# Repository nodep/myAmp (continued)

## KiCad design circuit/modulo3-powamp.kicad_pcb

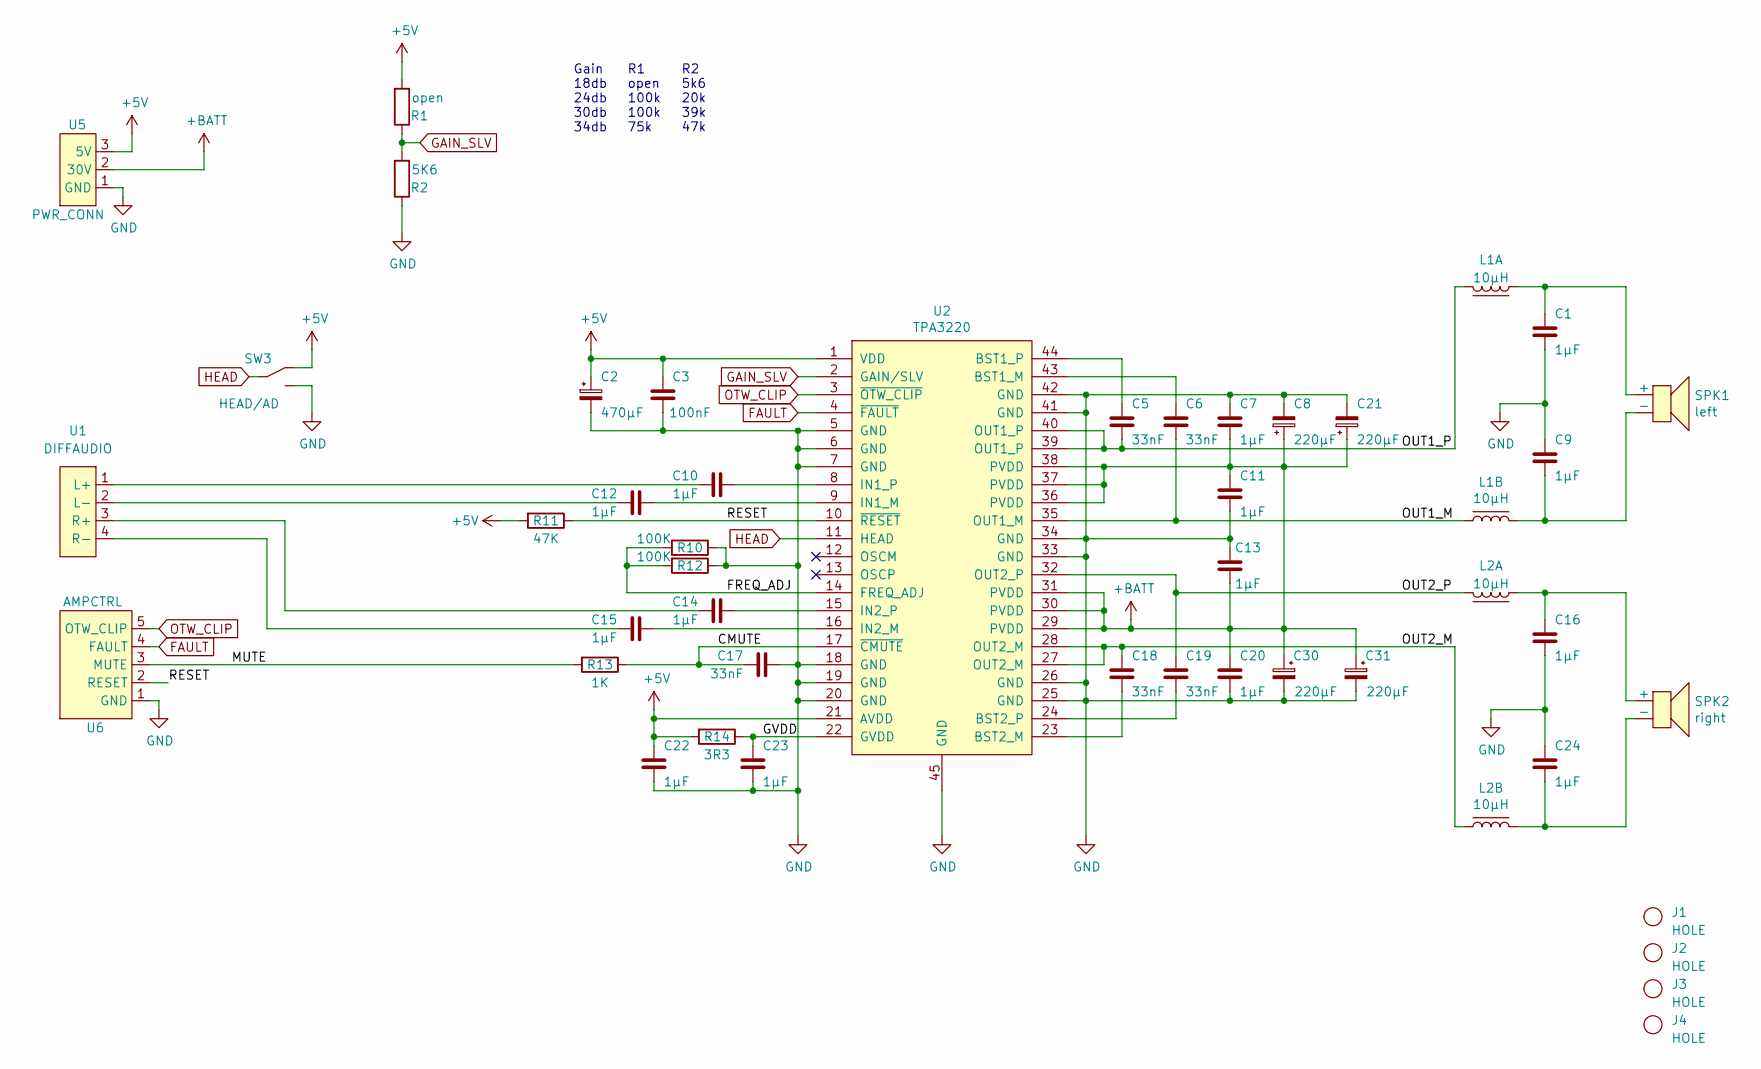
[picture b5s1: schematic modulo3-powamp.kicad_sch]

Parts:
C1, C9, C10, C12, C14, C15, C16, C24: 1μF; C_FILM_L7.2mm_W5.0mm_P5.00mm
C2: 470μF; CPOL_D8_P3.5
C3: 100nF; C_1206
C5, C6, C17, C18, C19: 33nF; C_1206
C7, C11, C13, C20, C22, C23: 1μF; C_1206
C8, C21, C30, C31: 220μF; CPOL_D10_P5
J1, J2, J3, J4: HOLE; MountingHole
L1, L2: 10μH; COILCRAFT-UA801x-AL
R1: open; R_10MM
R2: 5K6; R_10MM
R10, R12: 100K; R_10MM
R11: 47K; R_10MM
R13: 1K; R_10MM
R14: 3R3; R_0805
SPK1: left; SPKR_5MM_BLUE
SPK2: right; SPKR_5MM_BLUE
SW3: HEAD/AD; SW_SPDT_JUMPER
U1: DIFFAUDIO
U2: TPA3220; TSSOP-44_4.4x9.7mm_Pitch0.635mm_ThermalPad
U5: PWR_CONN
U6: AMPCTRL

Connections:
+5V: C2.1, C3.2, C22.1, R1.2, R11.2, R14.2, SW3.1, U2.1 (VDD), U2.21 (AVDD), U5.3 (5V)
+BATT: C7.2, C8.1, C11.1, C13.1, C20.1, C21.1, C30.1, C31.1, U2.29 (PVDD), U2.30 (PVDD), U2.31 (PVDD), U2.36 (PVDD), U2.37 (PVDD), U2.38 (PVDD), U5.2 (30V)
/CMUTE: C17.1, R13.1, U2.17 (~CMUTE)
/FREQ_ADJ: R10.2, R12.2, U2.14 (FREQ_ADJ)
/GVDD: C23.1, R14.1, U2.22 (GVDD)
/MUTE: R13.2, U6.3 (MUTE)
/OUT1_M: C6.2, L1.3, U2.35 (OUT1_M)
/OUT1_P: C5.2, L1.2, U2.39 (OUT1_P), U2.40 (OUT1_P)
/OUT2_M: C18.1, L2.3, U2.27 (OUT2_M), U2.28 (OUT2_M)
/OUT2_P: C19.1, L2.2, U2.32 (OUT2_P)
/RESET: R11.1, U2.10 (~RESET), U6.2 (RESET)
FAULT: U2.4 (~FAULT), U6.4 (FAULT)
GAIN_SLV: R1.1, R2.2, U2.2 (GAIN/SLV)
GND: C1.2, C2.2, C3.1, C7.1, C8.2, C9.1, C11.2, C13.2, C16.2, C17.2, C20.2, C21.2, C22.2, C23.2, C24.1, C30.2, C31.2, R2.1, R10.1, R12.1, SW3.3, U2.5 (GND), U2.6 (GND), U2.7 (GND), U2.18 (GND), U2.19 (GND), U2.20 (GND), U2.25 (GND), U2.26 (GND), U2.33 (GND), U2.34 (GND), U2.41 (GND), U2.42 (GND), U2.45 (GND), U5.1 (GND), U6.1 (GND)
HEAD: SW3.2, U2.11 (HEAD)
unnamed: C1.1, L1.1, SPK1.1 (+)
unnamed: C9.2, L1.4, SPK1.2 (-)
unnamed: C16.1, L2.1, SPK2.1 (+)
unnamed: C24.2, L2.4, SPK2.2 (-)
unnamed: C10.1, U1.1 (L+)
unnamed: C12.1, U1.2 (L-)
unnamed: C14.1, U1.3 (R+)
unnamed: C15.1, U1.4 (R-)
unnamed: C6.1, U2.43 (BST1_M)
unnamed: C5.1, U2.44 (BST1_P)
unnamed: C18.2, U2.23 (BST2_M)
unnamed: C19.2, U2.24 (BST2_P)
unnamed: C12.2, U2.9 (IN1_M)
unnamed: C10.2, U2.8 (IN1_P)
unnamed: C15.2, U2.16 (IN2_M)
unnamed: C14.2, U2.15 (IN2_P)
OTW_CLIP: U2.3 (~OTW_CLIP), U6.5 (OTW_CLIP)

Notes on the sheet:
Gain 18db 24db 30db 34db
R2 5k6 20k 39k 47k
R1 open 100k 100k 75k

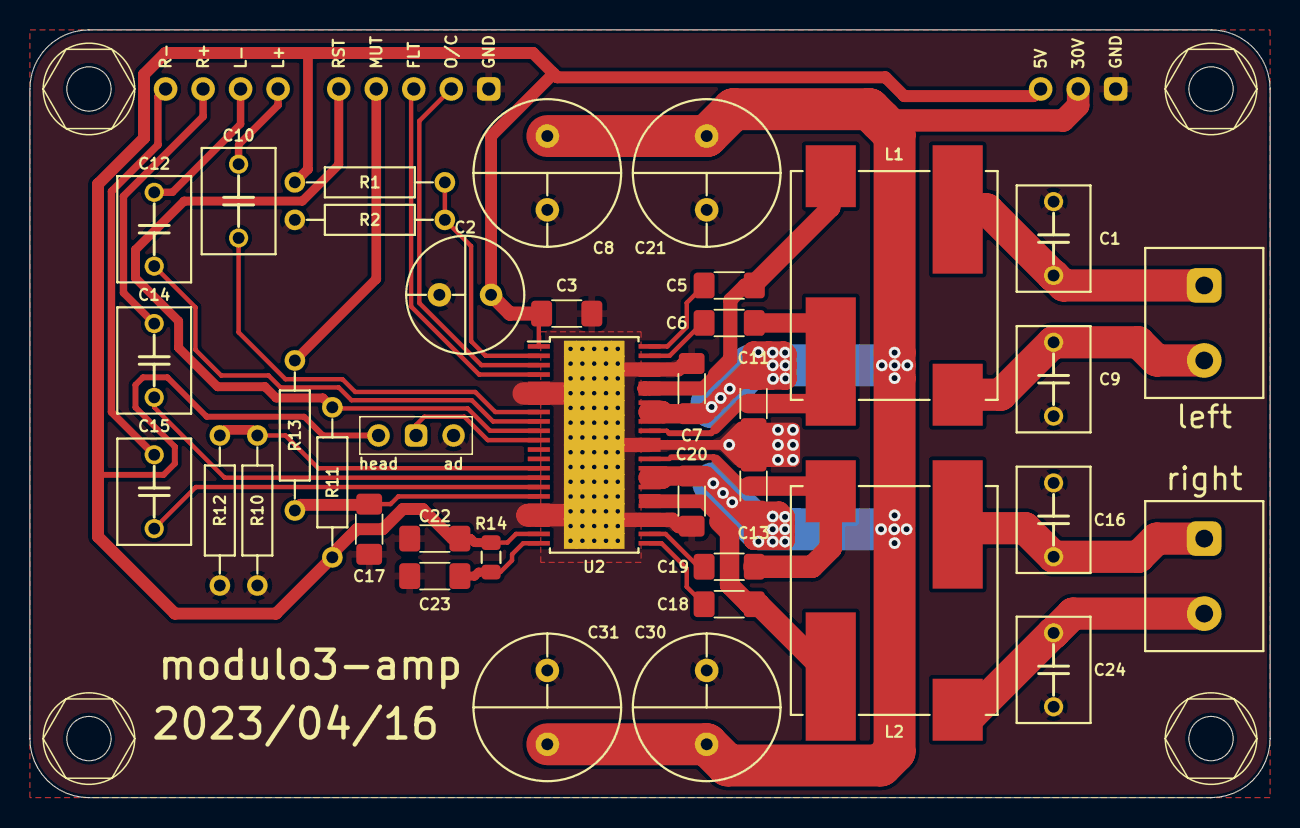
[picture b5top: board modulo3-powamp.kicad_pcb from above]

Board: 2 copper layers, 84.0 x 52.0 mm, 45 parts (0 on the bottom side), 32 nets.

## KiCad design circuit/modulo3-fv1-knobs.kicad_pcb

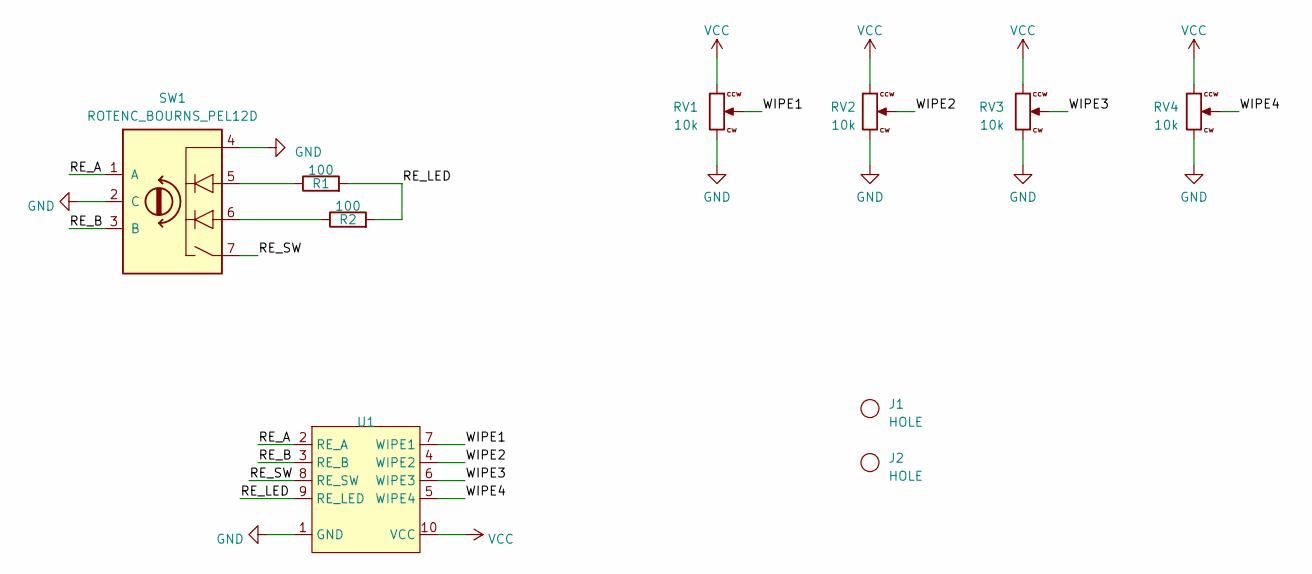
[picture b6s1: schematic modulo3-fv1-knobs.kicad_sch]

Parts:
J1, J2: HOLE; MountingHole
R1, R2: 100; R_10MM
RV1, RV2, RV3, RV4: 10k; BOURNS_PTD901_xx15K
SW1: ROTENC_BOURNS_PEL12D; BOURNS_PEL12D-2xxx
U1: KNOBS

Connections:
/RE_A: SW1.1 (A), U1.2 (RE_A)
/RE_B: SW1.3 (B), U1.3 (RE_B)
/RE_LED: R1.2, R2.2, U1.9 (RE_LED)
/RE_SW: SW1.7, U1.8 (RE_SW)
/WIPE1: RV1.2, U1.7 (WIPE1)
/WIPE2: RV2.2, U1.4 (WIPE2)
/WIPE3: RV3.2, U1.6 (WIPE3)
/WIPE4: RV4.2, U1.5 (WIPE4)
GND: RV1.3, RV2.3, RV3.3, RV4.3, SW1.2 (C), SW1.4, U1.1 (GND)
unnamed: R1.1, SW1.5
unnamed: R2.1, SW1.6
VCC: RV1.1, RV2.1, RV3.1, RV4.1, U1.10 (VCC)

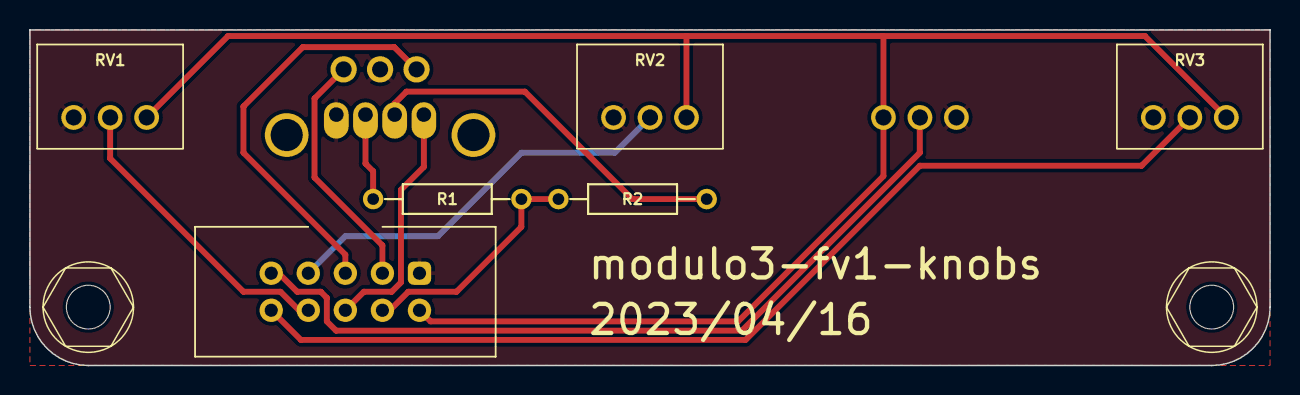
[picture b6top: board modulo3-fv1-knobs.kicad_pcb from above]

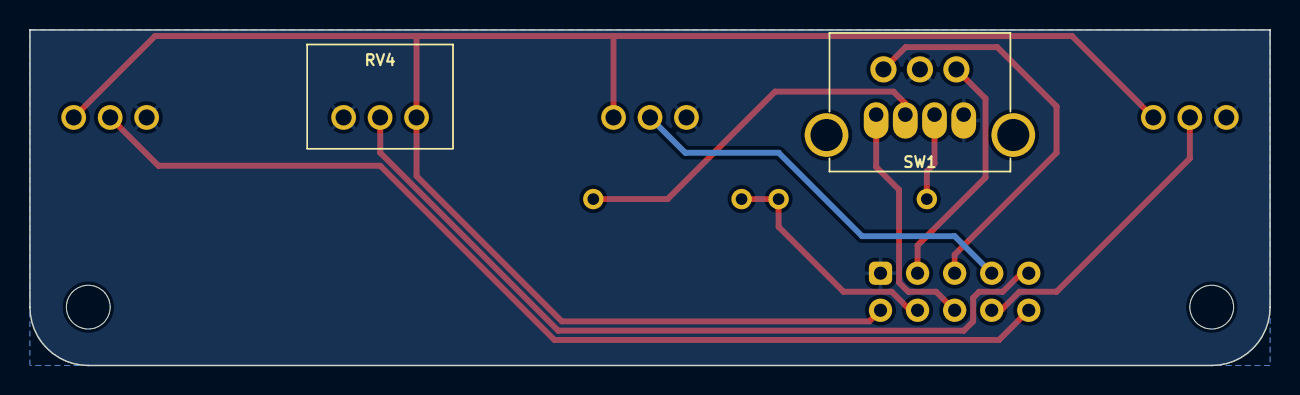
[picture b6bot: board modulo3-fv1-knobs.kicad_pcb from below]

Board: 2 copper layers, 85.0 x 23.0 mm, 10 parts (2 on the bottom side), 12 nets.

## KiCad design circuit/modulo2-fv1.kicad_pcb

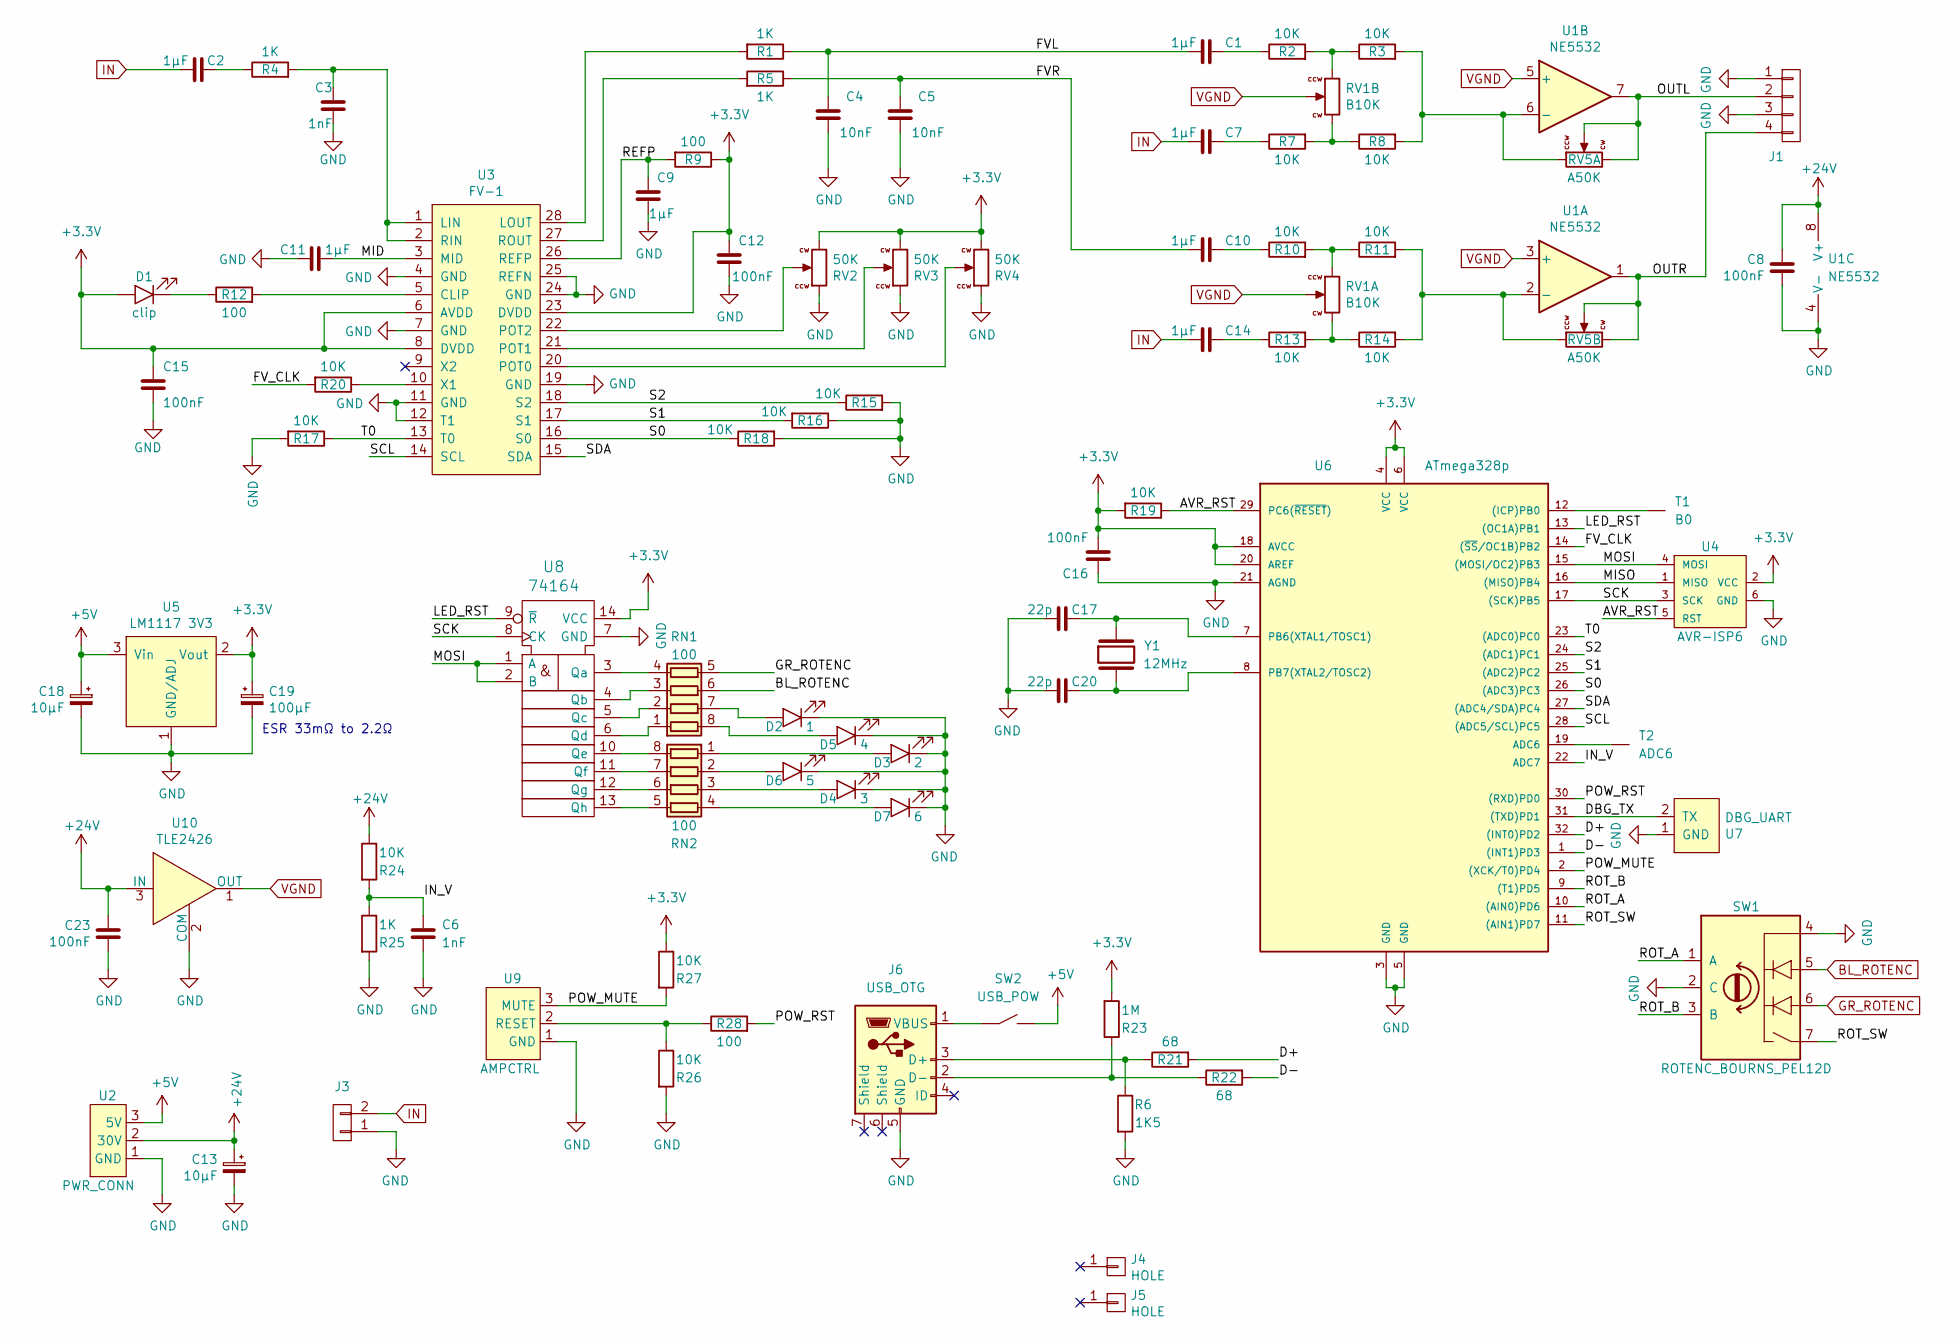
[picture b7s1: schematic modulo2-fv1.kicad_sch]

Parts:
C1, C2, C7, C10, C14: 1µF; C_FILM_L7.2mm_W5.0mm_P5.00mm
C3, C6: 1nF; C_1206
C4, C5: 10nF; C_1206
C8, C12, C15, C16: 100nF; C_1206
C9, C11: 1µF; C_1206
C13: 10µF; CPOL_D6.3_P2.5
C17, C20: 22p; C_5MM_1206
C18: 10µF; CPOL_D4_P1.5
C19: 100µF; CPOL_D6.3_P2.5
C23: 100nF; C_5MM_1206
D1: clip; LED_D3.0mm_Horizontal_Short
D2: 1; LED_D3.0mm_Horizontal_Long
D3: 2; LED_D3.0mm_Horizontal_Long
D4: 3; LED_D3.0mm_Horizontal_Long
D5: 4; LED_D3.0mm_Horizontal_Short
D6: 5; LED_D3.0mm_Horizontal_Short
D7: 6; LED_D3.0mm_Horizontal_Short
J1: CONN_01X04; PIN_1x04
J3: CONN_01X02; PIN_1x02
J4, J5: HOLE; MountingHole
J6: USB_OTG; USB_OTG_THT
R1, R5: 1K; R_1206
R2, R3, R7, R8, R10, R11, R13, R14: 10K; R_1206
R4, R25: 1K; R_10MM
R6: 1K5; R_10MM
R9, R12, R28: 100; R_10MM
R15, R16, R17, R18, R19, R20, R24, R26, R27: 10K; R_10MM
R21, R22: 68; R_10MM
R23: 1M; R_10MM
RN1, RN2: 100; R_Array_x4_1206
RV1: B10K; BOURNS_PTD902_xx15K
RV2, RV3, RV4: 50K; BOURNS_PTD901_xx15K
RV5: A50K; BOURNS_PTD902_xx15K
SW1: ROTENC_BOURNS_PEL12D; BOURNS_PEL12D-2xxx
SW2: USB_POW; PIN_1x02
T1: B0; TestPin
T2: ADC6; TestPin
U1: NE5532; SOIC-8_3.9x4.9mm_P1.27mm
U2: PWR_CONN
U3: FV-1; SOIC-28_7.5x17.9mm_Pitch1.27mm
U4: AVR-ISP6; AVR_ISP6
U5: LM1117 3V3; SOT-223
U6: ATmega328p; TQFP-32_7x7mm_Pitch0.8mm
U7: DBG_UART
U8: 74164; SOIC-14_3.9x8.7mm_P1.27mm
U9: AMPCTRL; PIN_1x03
U10: TLE2426; TO-92_Inline_Wide
Y1: 12MHz; Crystal_HC49-U_Vertical

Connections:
+3V3: C12.1, C15.2, C16.2, C19.1, D1.2 (A), R9.1, R19.2, R23.2, R27.1, RV2.3, RV3.3, RV4.3, U3.6 (AVDD), U3.8 (DVDD), U3.23 (DVDD), U4.2 (VCC), U5.2 (Vout), U6.4 (VCC), U6.6 (VCC), U6.18 (AVCC), U6.20 (AREF), U8.14 (VCC)
+5V: C18.1, SW2.2, U2.3 (5V), U5.3 (Vin)
+24V: C8.2, C13.1, C23.2, R24.1, U1.8 (V+), U2.2 (30V), U10.3 (IN)
/AVR_RST: R19.1, U4.5 (RST), U6.29 (PC6(~RESET))
/D+: R21.2, U6.32 ((INT0)PD2)
/D-: R22.2, U6.1 ((INT1)PD3)
/DBG_TX: U6.31 ((TXD)PD1), U7.2 (TX)
/FVL: C1.1, C4.1, R1.1
/FVR: C5.1, C10.1, R5.1
/FV_CLK: R20.2, U6.14 ((~SS/OC1B)PB2)
/IN_V: C6.2, R24.2, R25.1, U6.22 (ADC7)
/LED_RST: U6.13 ((OC1A)PB1), U8.9 (~R)
/MID: C11.2, U3.3 (MID)
/MISO: U4.1 (MISO), U6.16 ((MISO)PB4)
/MOSI: U4.4 (MOSI), U6.15 ((MOSI/OC2)PB3), U8.1 (A), U8.2 (B)
/OUTL: J1.2, RV5.2, RV5.3, U1.7
/OUTR: J1.4, RV5.5 (2), RV5.6 (3), U1.1
/POW_MUTE: R27.2, U6.2 ((XCK/T0)PD4), U9.3 (MUTE)
/POW_RST: R28.2, U6.30 ((RXD)PD0)
/REFP: C9.1, R9.2, U3.26 (REFP)
/ROT_A: SW1.1 (A), U6.10 ((AIN0)PD6)
/ROT_B: SW1.3 (B), U6.9 ((T1)PD5)
/ROT_SW: SW1.7, U6.11 ((AIN1)PD7)
/S0: R18.1, U3.16 (S0), U6.26 ((ADC3)PC3)
/S1: R16.2, U3.17 (S1), U6.25 ((ADC2)PC2)
/S2: R15.1, U3.18 (S2), U6.24 ((ADC1)PC1)
/SCK: U4.3 (SCK), U6.17 ((SCK)PB5), U8.8 (CK)
/SCL: U3.14 (SCL), U6.28 ((ADC5/SCL)PC5)
/SDA: U3.15 (SDA), U6.27 ((ADC4/SDA)PC4)
/T0: R17.1, U3.13 (T0), U6.23 ((ADC0)PC0)
BL_ROTENC: RN1.6 (R3.2), SW1.5
GND: C3.1, C4.2, C5.2, C6.1, C8.1, C9.2, C11.1, C12.2, C13.2, C15.1, C16.1, C17.2, C18.2, C19.2, C20.2, C23.1, D2.1 (K), D3.1 (K), D4.1 (K), D5.1 (K), D6.1 (K), D7.1 (K), J1.1, J1.3, J3.1, J6.5 (GND), R6.2, R15.2, R16.1, R17.2, R18.2, R25.2, R26.2, RV2.1, RV3.1, RV4.1, SW1.2 (C), SW1.4, U1.4 (V-), U2.1 (GND), U3.4 (GND), U3.7 (GND), U3.11 (GND), U3.12 (T1), U3.19 (GND), U3.24 (GND), U3.25 (REFN), U4.6 (GND), U5.1 (GND/ADJ), U6.3 (GND), U6.5 (GND), U6.21 (AGND), U7.1 (GND), U8.7 (GND), U9.1 (GND), U10.2 (COM)
GR_ROTENC: RN1.5 (R4.2), SW1.6
IN: C2.2, C7.1, C14.1, J3.2
unnamed: C1.2, R2.1
unnamed: C2.1, R4.1
unnamed: C3.2, R4.2, U3.1 (LIN), U3.2 (RIN)
unnamed: C7.2, R7.1
unnamed: C10.2, R10.1
unnamed: C14.2, R13.1
unnamed: C17.1, U6.7 (PB6(XTAL1/TOSC1)), Y1.1
unnamed: C20.1, U6.8 (PB7(XTAL2/TOSC2)), Y1.2
unnamed: D1.1 (K), R12.1
unnamed: D2.2 (A), RN1.7 (R2.2)
unnamed: D3.2 (A), RN2.1 (R1.1)
unnamed: D4.2 (A), RN2.3 (R3.1)
unnamed: D5.2 (A), RN1.8 (R1.2)
unnamed: D6.2 (A), RN2.2 (R2.1)
unnamed: D7.2 (A), RN2.4 (R4.1)
unnamed: J6.1 (VBUS), SW2.1
unnamed: J6.2 (D-), R22.1, R23.1
unnamed: J6.3 (D+), R6.1, R21.1
unnamed: R1.2, U3.28 (LOUT)
unnamed: R2.2, R3.1, RV1.4 (1)
unnamed: R3.2, R8.2, RV5.1, U1.6 (-)
unnamed: R5.2, U3.27 (ROUT)
unnamed: R7.2, R8.1, RV1.6 (3)
unnamed: R10.2, R11.1, RV1.1
unnamed: R11.2, R14.2, RV5.4 (1), U1.2 (-)
unnamed: R12.2, U3.5 (CLIP)
unnamed: R13.2, R14.1, RV1.3
unnamed: R20.1, U3.10 (X1)
unnamed: R26.1, R28.1, U9.2 (RESET)
unnamed: RN1.1 (R1.1), U8.6 (Qd)
unnamed: RN1.2 (R2.1), U8.5 (Qc)
unnamed: RN1.3 (R3.1), U8.4 (Qb)
unnamed: RN1.4 (R4.1), U8.3 (Qa)
unnamed: RN2.5 (R4.2), U8.13 (Qh)
unnamed: RN2.6 (R3.2), U8.12 (Qg)
unnamed: RN2.7 (R2.2), U8.11 (Qf)
unnamed: RN2.8 (R1.2), U8.10 (Qe)
unnamed: RV2.2, U3.22 (POT2)
unnamed: RV3.2, U3.21 (POT1)
unnamed: RV4.2, U3.20 (POT0)
unnamed: T1.1, U6.12 ((ICP)PB0)
unnamed: T2.1, U6.19 (ADC6)
VGND: RV1.2, RV1.5 (2), U1.3 (+), U1.5 (+), U10.1 (OUT)

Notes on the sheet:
ESR 33mΩ to 2.2Ω

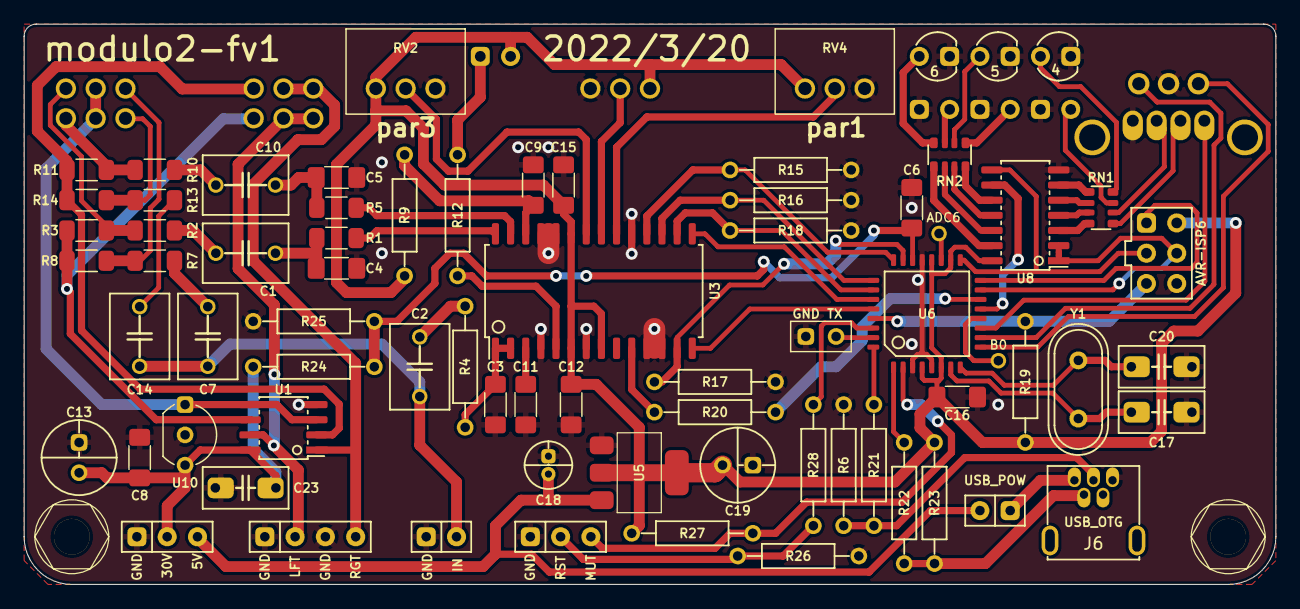
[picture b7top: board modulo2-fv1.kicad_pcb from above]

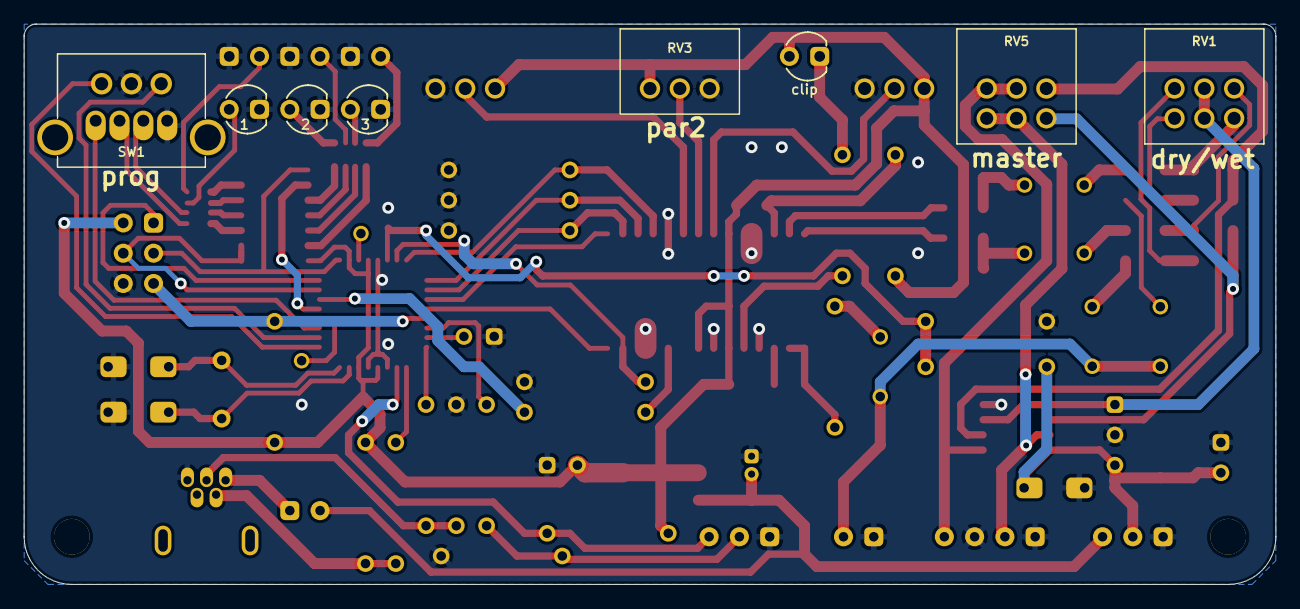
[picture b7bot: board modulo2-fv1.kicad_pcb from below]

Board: 2 copper layers, 105.0 x 47.0 mm, 83 parts (8 on the bottom side), 77 nets.

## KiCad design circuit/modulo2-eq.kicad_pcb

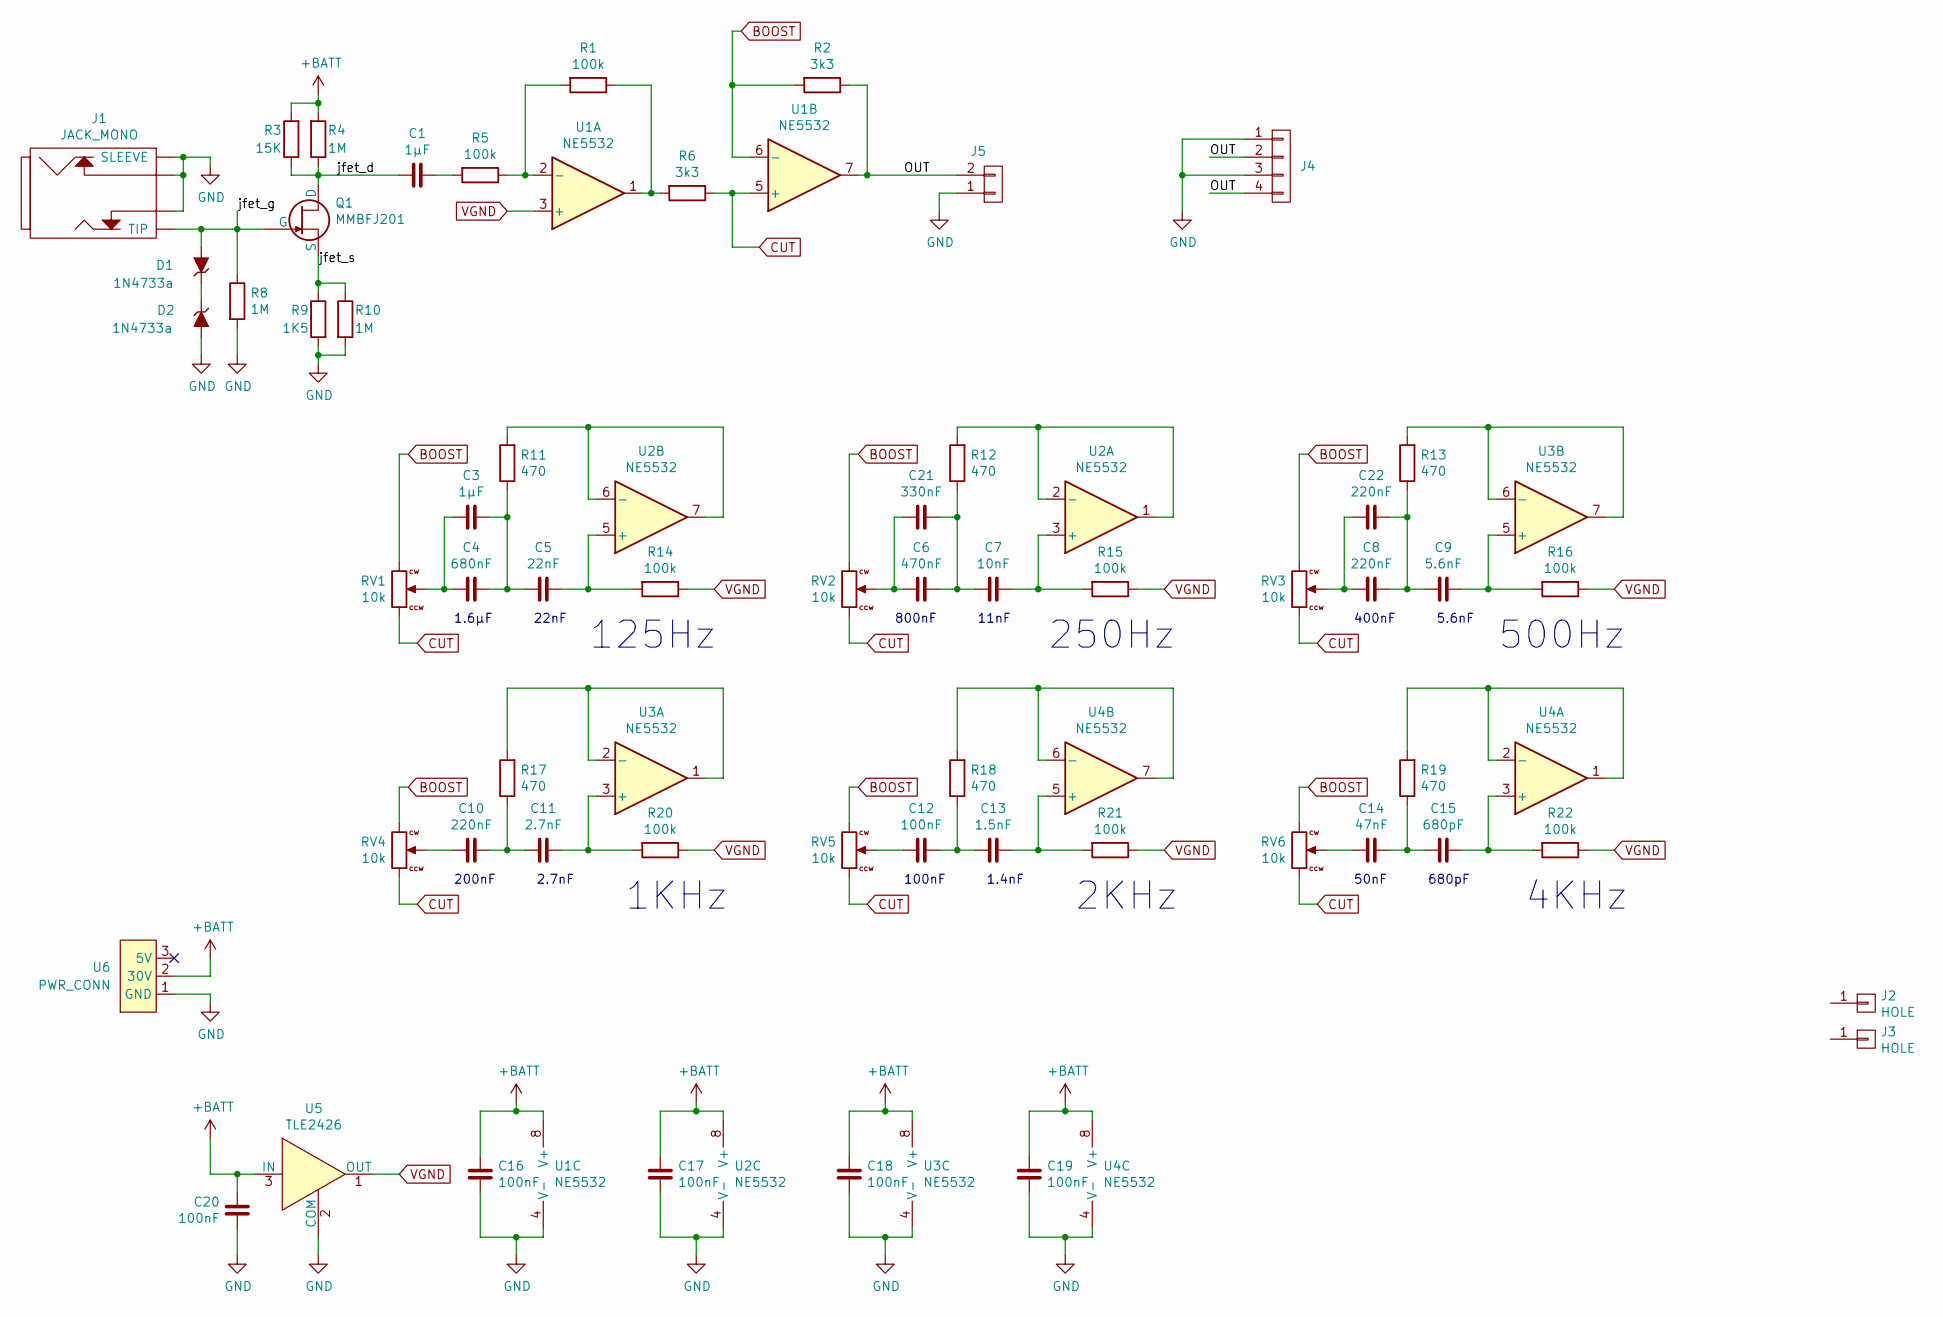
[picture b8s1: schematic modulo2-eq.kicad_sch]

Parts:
C1, C3: 1μF; C_FILM_L7.2mm_W5.0mm_P5.00mm
C4: 680nF; C_FILM_L7.2mm_W4.5mm_P5.00mm
C5: 22nF; C_5MM_1206
C6: 470nF; C_FILM_L7.2mm_W4.5mm_P5.00mm
C7: 10nF; C_5MM_1206
C8, C10: 220nF; C_FILM_L7.2mm_W3.5mm_P5.00mm
C9: 5.6nF; C_5MM_1206
C11: 2.7nF; C_5MM_1206
C12: 100nF; C_FILM_L7.2mm_W3.5mm_P5.00mm
C13: 1.5nF; C_5MM_1206
C14: 47nF; C_5MM_1206
C15: 680pF; C_5MM_1206
C16, C17, C19, C20: 100nF; C_1206
C18: 100nF; C_FILM_L7.2mm_W2.5mm_P5.00mm
C21: 330nF; C_FILM_L7.2mm_W4.5mm_P5.00mm
C22: 220nF; C_FILM_L7.2mm_W4.5mm_P5.00mm
D1, D2: 1N4733a; DO41
J1: JACK_MONO; JACK_CL13106
J2, J3: HOLE; MountingHole
J4: CONN_01X04; PIN_1x04
J5: CONN_01X02; PIN_1x02
Q1: MMBFJ201; SOT-23_with_jig
R1, R5, R14, R15, R16, R20, R21, R22: 100k; R_10MM
R2, R6: 3k3; R_10MM
R3: 15K; R_10MM
R4, R8, R10: 1M; R_10MM
R9: 1K5; R_10MM
R11, R12, R13, R17, R18, R19: 470; R_10MM
RV1, RV2, RV3, RV4, RV5, RV6: 10k; BOURNS_PTD901_xx15K
U1, U2, U3, U4: NE5532; SOIC-8_3.9x4.9mm_P1.27mm
U5: TLE2426; TO-92_Inline_Wide
U6: PWR_CONN

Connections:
+BATT: C16.2, C17.2, C18.2, C19.2, C20.2, R3.2, R4.2, U1.8 (V+), U2.8 (V+), U3.8 (V+), U4.8 (V+), U5.3 (IN), U6.2 (30V)
/OUT: J4.2, J4.4, J5.2, R2.1, U1.7
/jfet_d: C1.2, Q1.1 (D), R3.1, R4.1
/jfet_g: D1.2 (A), J1.6 (TIP), Q1.3 (G), R8.1
/jfet_s: Q1.2 (S), R9.1, R10.1
BOOST: R2.2, RV1.3, RV2.3, RV3.3, RV4.3, RV5.3, RV6.3, U1.6 (-)
CUT: R6.1, RV1.1, RV2.1, RV3.1, RV4.1, RV5.1, RV6.1, U1.5 (+)
GND: C16.1, C17.1, C18.1, C19.1, C20.1, D2.2 (A), J1.1, J1.3, J1.4 (SLEEVE), J4.1, J4.3, J5.1, R8.2, R9.2, R10.2, U1.4 (V-), U2.4 (V-), U3.4 (V-), U4.4 (V-), U5.2 (COM), U6.1 (GND)
unnamed: C1.1, R5.2
unnamed: C3.1, C4.1, C5.2, R11.1
unnamed: C3.2, C4.2, RV1.2
unnamed: C5.1, R14.2, U2.5 (+)
unnamed: C7.1, R15.2, U2.3 (+)
unnamed: C9.1, R16.2, U3.5 (+)
unnamed: C10.1, C11.2, R17.1
unnamed: C10.2, RV4.2
unnamed: C11.1, R20.2, U3.3 (+)
unnamed: C12.1, C13.2, R18.1
unnamed: C12.2, RV5.2
unnamed: C13.1, R21.2, U4.5 (+)
unnamed: C14.1, C15.2, R19.1
unnamed: C14.2, RV6.2
unnamed: C15.1, R22.2, U4.3 (+)
unnamed: C6.1, C7.2, C21.1, R12.1
unnamed: C6.2, C21.2, RV2.2
unnamed: C8.1, C9.2, C22.1, R13.1
unnamed: C8.2, C22.2, RV3.2
unnamed: D1.1 (K), D2.1 (K)
unnamed: R1.1, R6.2, U1.1
unnamed: R1.2, R5.1, U1.2 (-)
unnamed: R11.2, U2.6 (-), U2.7
unnamed: R12.2, U2.1, U2.2 (-)
unnamed: R13.2, U3.6 (-), U3.7
unnamed: R17.2, U3.1, U3.2 (-)
unnamed: R18.2, U4.6 (-), U4.7
unnamed: R19.2, U4.1, U4.2 (-)
VGND: R14.1, R15.1, R16.1, R20.1, R21.1, R22.1, U1.3 (+), U5.1 (OUT)

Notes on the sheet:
100nF 1.4nF
200nF 2.7nF
4KHz
1.6μF 22nF
250Hz
50nF 680pF
800nF 11nF
400nF 5.6nF
1KHz
500Hz
2KHz
125Hz

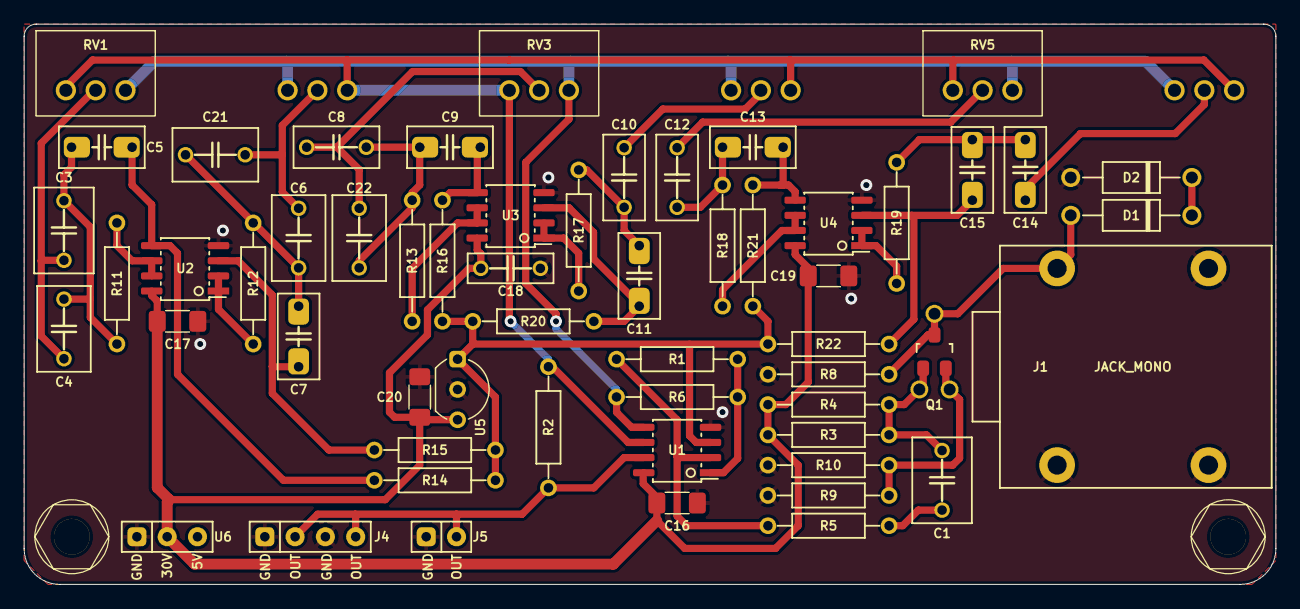
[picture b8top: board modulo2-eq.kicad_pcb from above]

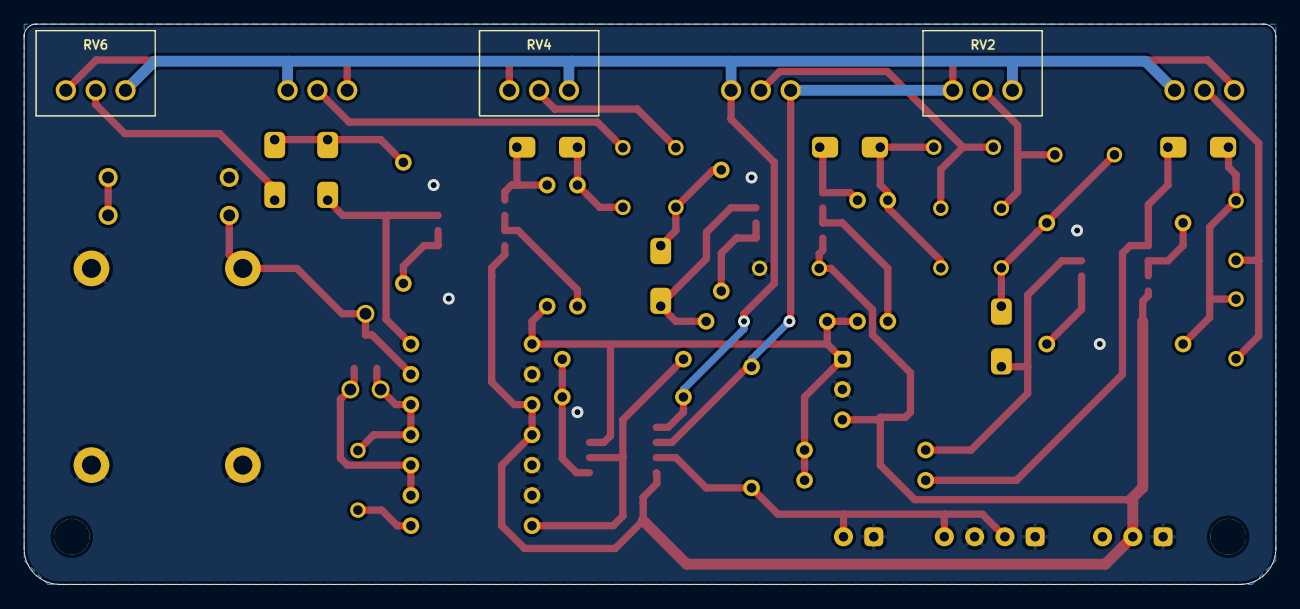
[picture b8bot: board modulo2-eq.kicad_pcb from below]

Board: 2 copper layers, 105.0 x 47.0 mm, 62 parts (3 on the bottom side), 37 nets.

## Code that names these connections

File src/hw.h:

#pragma once

#include "iopin.h"
#include "timera.h"
#include "usart.h"
#include "spimaster.h"
#include "i2c.h"
#include "watch.h"

// screen & touchscreen
using s_led		= IoPin<'A', 7>;
using s_cs		= IoPin<'B', 0>;
using s_rst		= IoPin<'B', 1>;
using s_dc		= IoPin<'B', 2>;
using s_mosi	= IoPin<'B', 4>;
using s_miso	= IoPin<'B', 5>;
using s_sck		= IoPin<'B', 6>;

using ts_cs		= IoPin<'B', 3>;
using ts_irq	= IoPin<'B', 7>;

using s_spi		= SpiMaster<1, 6>;

// FV-1
using fv1_clip		= IoPin<'E', 6>;
using fv1_t0		= IoPin<'E', 7>;
using fv1_s0		= IoPin<'F', 4>;
using fv1_s1		= IoPin<'F', 5>;	// these two are swapped on the latest PCB version
using fv1_s2		= IoPin<'G', 3>;	// these two are swapped on the latest PCB version
using fv1_p0		= IoPin<'G', 0>;
using fv1_p1		= IoPin<'G', 1>;
using fv1_p2		= IoPin<'G', 2>;
using fv1_sda		= IoPin<'F', 2>;
using fv1_scl		= IoPin<'F', 3>;
using fv1_i2c		= I2CSlave<1>;

// digipot mix
using dp_mix_sda	= IoPin<'C', 2>;
using dp_mix_scl	= IoPin<'C', 3>;
using dp_mix_i2c	= I2CMaster<0>;

const uint8_t dp_mix_address = 0b101111;

// PWM for FV-1 pots
using fv1_pwm_timer	= TimerA<0, 1>;

// FV-1 knobs
using fv1k_led		= IoPin<'D', 3>;
using fv1k_re_a		= IoPin<'D', 4>;
using fv1k_re_sw	= IoPin<'D', 5>;
using fv1k_re_b		= IoPin<'D', 6>;
using fv1k_pot1		= IoPin<'E', 2>;
using fv1k_pot2		= IoPin<'E', 3>;
using fv1k_pot3		= IoPin<'E', 4>;
using fv1k_pot4		= IoPin<'E', 5>;

// power amp
using pa_fault		= IoPin<'A', 0>;
using pa_reset		= IoPin<'A', 1>;
using pa_mute		= IoPin<'A', 2>;
using pa_otw_clip	= IoPin<'G', 7>;

// pedals/footswitches UART
using pdl_tx		= IoPin<'E', 0>;
using pdl_rx		= IoPin<'E', 1>;
using pdl_usart		= Usart<4>;

// misc
using in_v			= IoPin<'D', 7>;
using dbg_tx		= IoPin<'A', 4>;
using dbg_pin		= IoPin<'A', 3>;

// timekeeping: 1 tick == 0.24ms
using Watch = RTClock<8>;

using DebugUsart = Usart<0>;

void init_hw();

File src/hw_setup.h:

#pragma once

// the LED shift registers
#define LED_DATA_PORT	B
#define LED_DATA_BIT	3

#define LED_CLOCK_PORT	B
#define LED_CLOCK_BIT	5

#define LED_RST_PORT	B
#define LED_RST_BIT		1

// output pins for selecting the program on the FV-1
// S0, S1 and S2 must be on the same port!!!
#define S0_PORT			C
#define S0_BIT			3

#define S1_PORT			C
#define S1_BIT			2

#define S2_PORT			C
#define S2_BIT			1

#define T0_PORT			C
#define T0_BIT			0

// FV_CLK clock for the FV-1
#define FV_CLK_PORT		B
#define FV_CLK_BIT		2

// rotary encoder
#define ROT_SW_PORT		D
#define ROT_SW_BIT		7

#define ROT_A_PORT		D
#define ROT_A_BIT		6

#define ROT_B_PORT		D
#define ROT_B_BIT		5

// the power amp supervisor
#define PS_MUTE_PORT	D
#define PS_MUTE_BIT		4

#define PS_RESET_PORT	D
#define PS_RESET_BIT	0

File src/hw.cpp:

#include <avr/io.h>
#include <util/delay.h>

#include "hw.h"
#include "avrdbg.h"
#include "powamp.h"
#include "fv1.h"
#include "adc.h"

void mcu_init()
{
	CPU_CCP = CCP_IOREG_gc;
#if   F_CPU == 1000000
	CLKCTRL.OSCHFCTRLA = CLKCTRL_AUTOTUNE_bm | CLKCTRL_FRQSEL_1M_gc;
#elif F_CPU == 2000000
	CLKCTRL.OSCHFCTRLA = CLKCTRL_AUTOTUNE_bm | CLKCTRL_FRQSEL_2M_gc;
#elif F_CPU == 3000000
	CLKCTRL.OSCHFCTRLA = CLKCTRL_AUTOTUNE_bm | CLKCTRL_FRQSEL_3M_gc;
#elif F_CPU == 4000000
	CLKCTRL.OSCHFCTRLA = CLKCTRL_AUTOTUNE_bm | CLKCTRL_FRQSEL_4M_gc;
#elif F_CPU == 8000000
	CLKCTRL.OSCHFCTRLA = CLKCTRL_AUTOTUNE_bm | CLKCTRL_FRQSEL_8M_gc;
#elif F_CPU == 12000000
	CLKCTRL.OSCHFCTRLA = CLKCTRL_AUTOTUNE_bm | CLKCTRL_FRQSEL_12M_gc;
#elif F_CPU == 16000000
	CLKCTRL.OSCHFCTRLA = CLKCTRL_AUTOTUNE_bm | CLKCTRL_FRQSEL_16M_gc;
#elif F_CPU == 20000000
	CLKCTRL.OSCHFCTRLA = CLKCTRL_AUTOTUNE_bm | CLKCTRL_FRQSEL_20M_gc;
#elif F_CPU == 24000000
	CLKCTRL.OSCHFCTRLA = CLKCTRL_AUTOTUNE_bm | CLKCTRL_FRQSEL_24M_gc;
#else
	#error Unknown F_CPU setting
#endif

	
	////////////////
	// MCU pin mux
	////////////////

	// debug TX on UART
	PORTMUX.USARTROUTEA = PORTMUX_USART0_0_bm;	// ALT -> PA4 is TX

	// SPI for display/touchscreen
	PORTMUX.SPIROUTEA = PORTMUX_SPI1_1_bm;		// ALT2 -> PB4 is MOSI...

	// I2C for digi pots
	PORTMUX.TWIROUTEA = PORTMUX_TWI0_1_bm;		// ALT2 -> PC2 is SDA, PC3 is SCL

	// PWM for FV-1 pots
	PORTMUX.TCAROUTEA = 6;		// PWM WaveOut on PORTG
}

void init_hw()
{
	mcu_init();
	dbgInit();

	dbg_pin::dir_out();
	dbg_pin::high();

	Watch::start();

	ADC::init();

	powamp_init();
}
